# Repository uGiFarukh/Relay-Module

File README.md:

# Relay-Module

Basic 1 Channel Relay Module designed in AutoDesk Eagle. Operates under small signal from any microcontroller. Based on relay coil voltage of 12 volts.
<br />
<br />
<br />
<br />
<br />
Special thanks to Carlos Santiago from [[CHS_Electronics](https://www.youtube.com/channel/UCcNpRuzeedQ9Ps3xF4RDMaw)] & AnalogKid from [[Electronics Point](https://www.electronicspoint.com)]

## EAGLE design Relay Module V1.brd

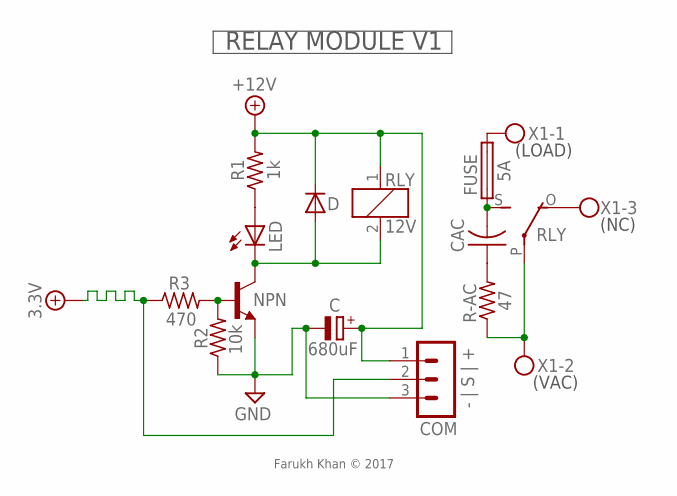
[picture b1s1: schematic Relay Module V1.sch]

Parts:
C: 680uF; E3,5-10
CAC: C-US150-064X183; C150-064X183
COM: - | S | +; MA03-1
D: 1N4004; DO41-10
FUSE: 5A; SH22
LED: LED3MM
NPN: 2N2222A; TO18
R1: 1k; 0204/7
R2: 10k; 0204/7
R3: 470; 0204/7
R-AC: 47; 0617/17
RLY: 12V; G5LE
X1: MKDSN1,5/3-5,08

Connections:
+5V: COM.2, R3.1
+12V: C.+, COM.1, D.C, R1.2, RLY.1
GND: C.-, COM.3, NPN.1 (E), R2.1
unnamed: LED.A, R1.1
unnamed: D.A, LED.K (C), NPN.3 (C), RLY.2
unnamed: NPN.2 (B), R2.2, R3.2
unnamed: FUSE.2, X1.1
unnamed: R-AC.1, RLY.P, X1.2
unnamed: CAC.1, R-AC.2
unnamed: CAC.2, FUSE.1, RLY.S
unnamed: RLY.O, X1.3

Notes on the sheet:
RELAY MODULE V1
Farukh Khan © 2017
(LOAD)
(VAC)
(NC)

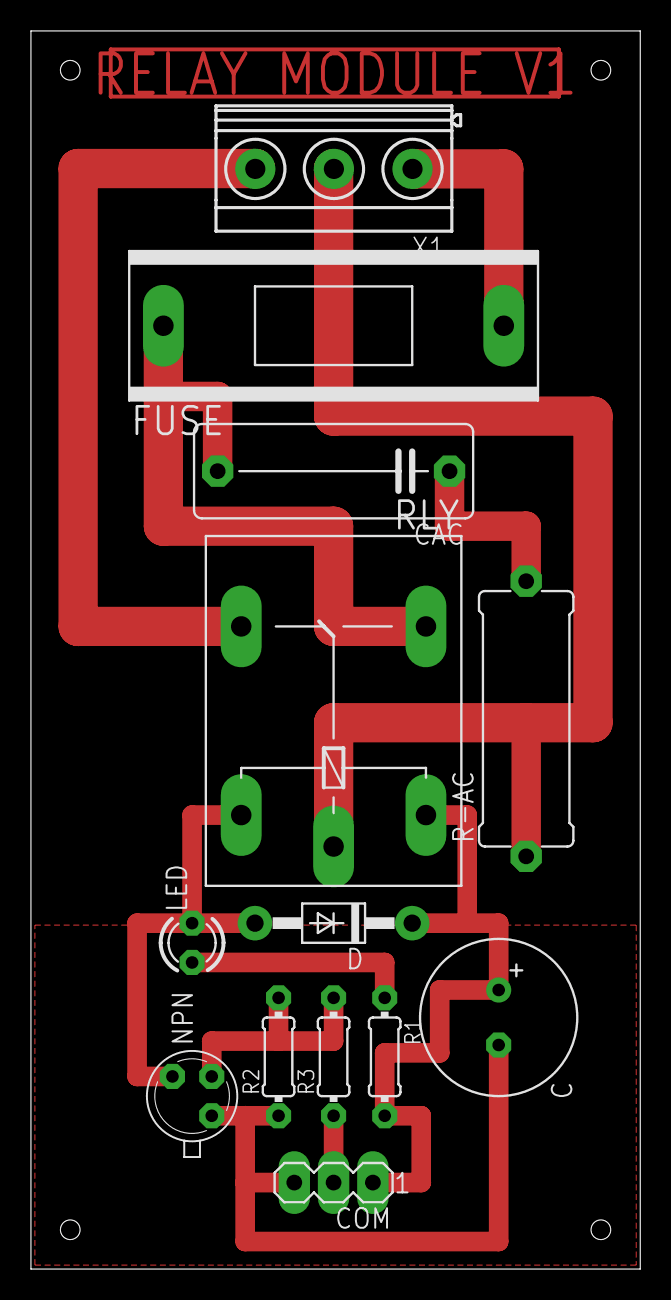
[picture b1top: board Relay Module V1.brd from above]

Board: 2 copper layers, 39.4 x 80.0 mm, 13 parts (0 on the bottom side), 11 nets.

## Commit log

2017-12-31 Eagle Source Files
    Uploaded AutoDesk Eagle Source Files !!!
2017-12-31 Update README.md
    Credits added !
2018-01-01 Update README.md
    Some minor corrections...
